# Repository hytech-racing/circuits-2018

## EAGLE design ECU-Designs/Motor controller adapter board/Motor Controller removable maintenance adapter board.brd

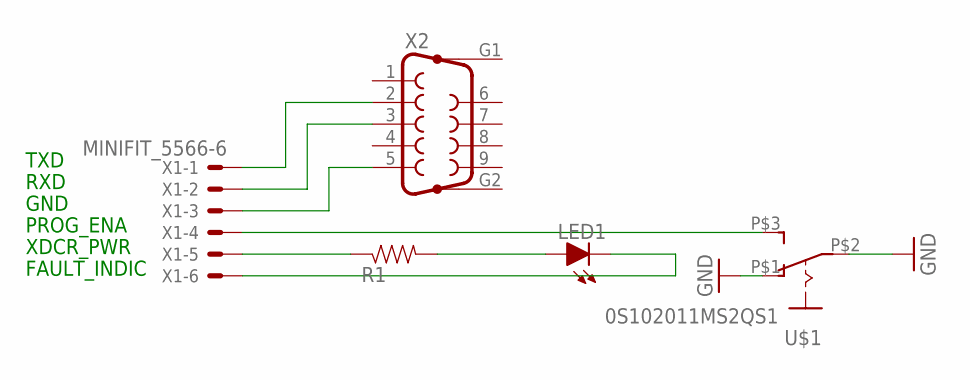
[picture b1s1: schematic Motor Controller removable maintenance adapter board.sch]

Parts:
LED1: LED-0805; LED-805
R1: RESISTOR0805-RES; 0805
U$1: 0S102011MS2QS1
X1: MINIFIT_5566-6
X2: F09HP

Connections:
GND: U$1.P$1 (O), U$1.P$2
unnamed: LED1.A, R1.2
unnamed: R1.1, X1.5
unnamed: LED1.C, X1.6
unnamed: U$1.P$3 (S), X1.4
unnamed: X1.1, X2.2
unnamed: X1.2, X2.3
unnamed: X1.3, X2.5

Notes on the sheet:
TXD
RXD
GND
PROG_ENA
XDCR_PWR
FAULT_INDIC

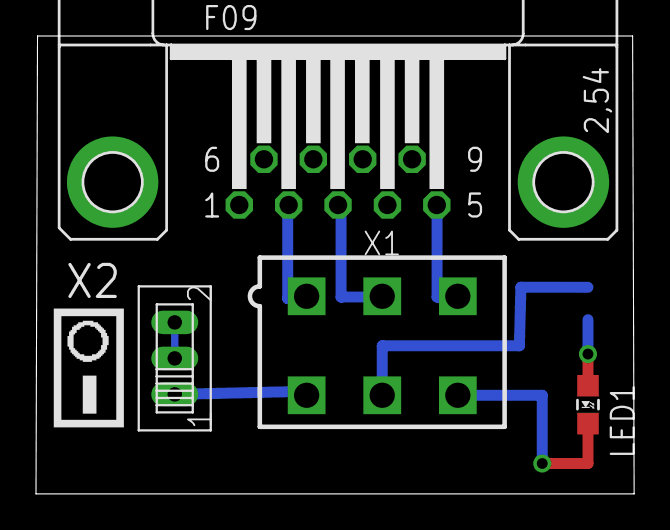
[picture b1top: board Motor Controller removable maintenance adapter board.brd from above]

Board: 2 copper layers, 33.2 x 25.4 mm, 5 parts (1 on the bottom side), 8 nets.

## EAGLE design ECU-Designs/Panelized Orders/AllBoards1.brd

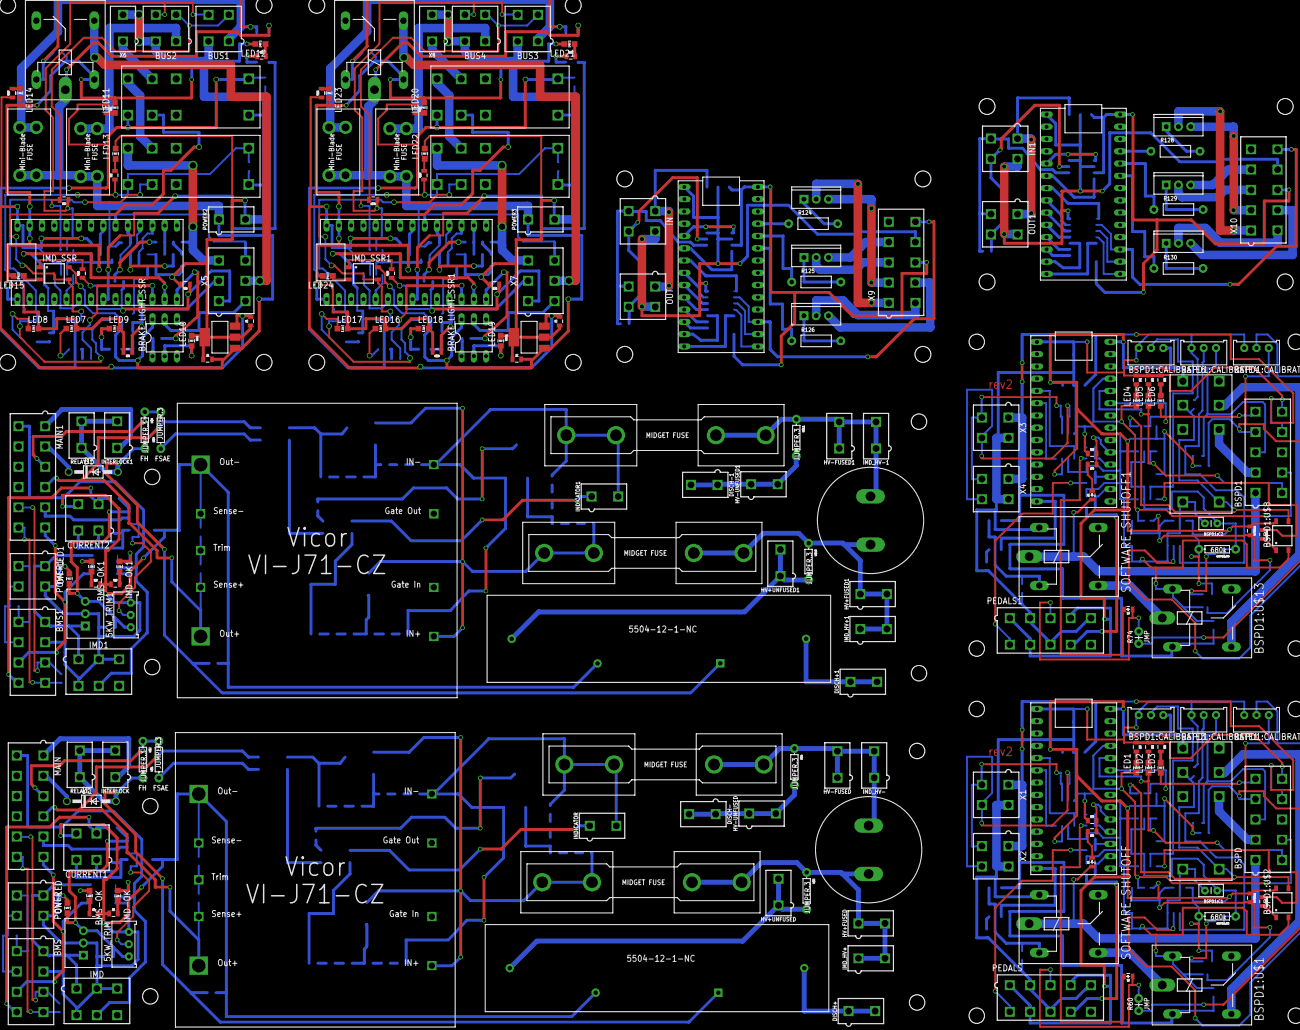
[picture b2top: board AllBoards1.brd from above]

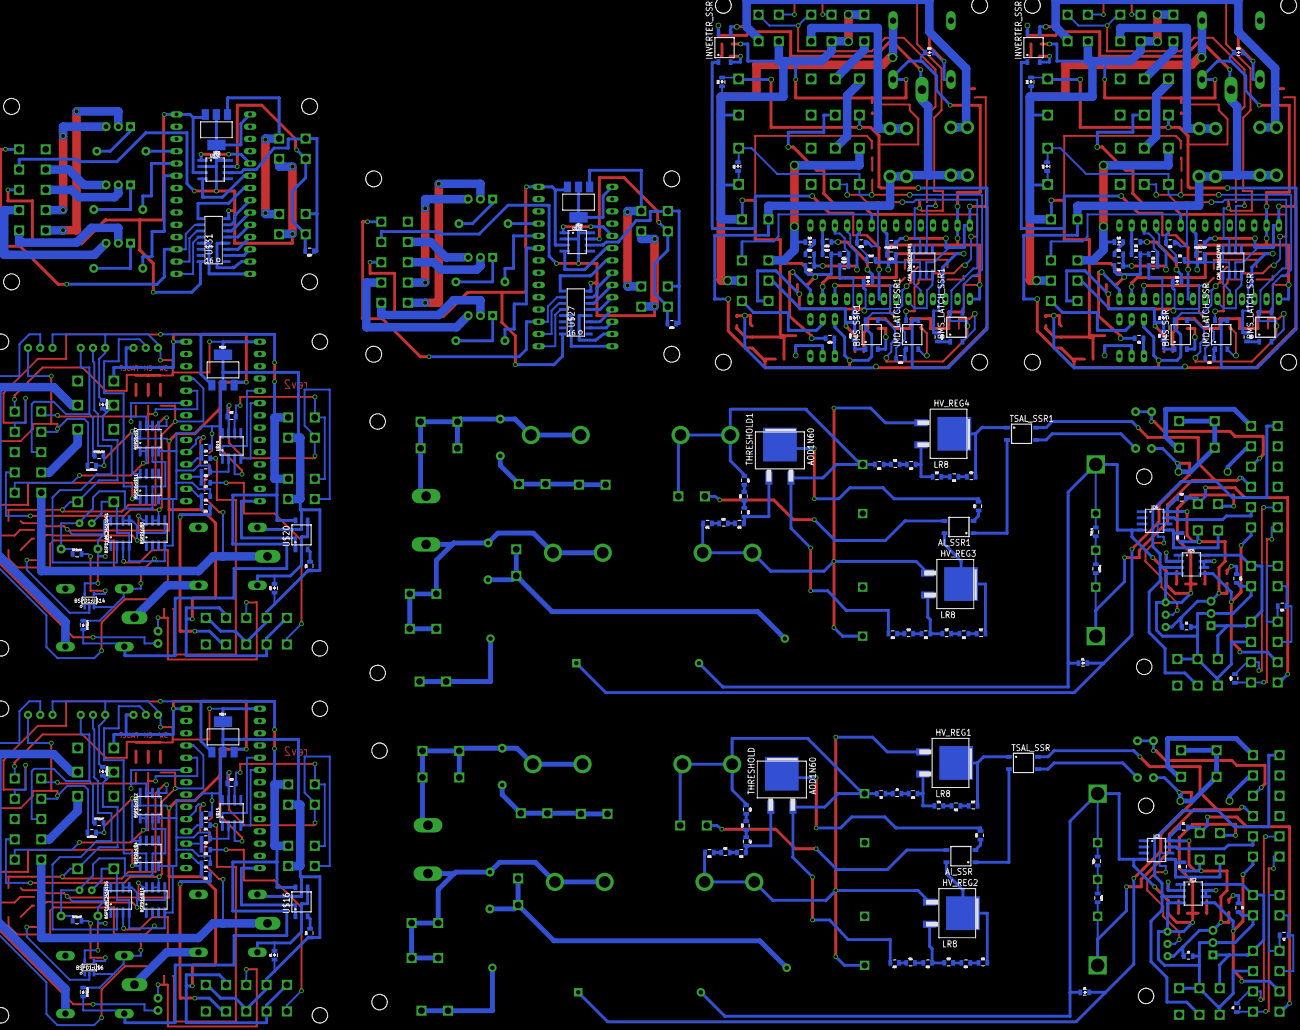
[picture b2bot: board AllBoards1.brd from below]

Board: 2 copper layers, 378 parts (172 on the bottom side), 344 nets.

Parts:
5KW_TRIM, 5KW_TRIM1: TRIMPOT_3296
AI_SSR, AI_SSR1: CPC1002N; SOP04
BMS, BMS1: MINIFIT_5566-8
BMS-OK, BMS-OK1: LED-805
BMS_LATCH_SSR, BMS_LATCH_SSR1: CPC1002N; SOP04
BMS_SSR, BMS_SSR1: CPC1002N; SOP04
BOARD_TEMP, BOARD_TEMP1: THERMISTOR_NCP21; 0805
BRAKE_LIGHT_SSR, BRAKE_LIGHT_SSR1: SOLID_STATE_RELAY_VO14642AT; DIL06
BSPD, BSPD1: MINIFIT_5566-10
BSPD1:C1, BSPD1:C2: .47u; CAP-PTH-SMALLEZ
BSPD1:CALIBRATE1, BSPD1:CALIBRATE2, BSPD1:CALIBRATE3, BSPD1:CALIBRATE4, BSPD1:CALIBRATE5, BSPD1:CALIBRATE6: TRIMPOT_3296
BSPD1:D1, BSPD1:D2, BSPD1:D3, BSPD1:D4: DIODE0805; 0805_D
BSPD1:MC34161DG, BSPD1:MC34161DG1: SOIC-08
BSPD1:R1, BSPD1:R2, BSPD1:R4, BSPD1:R7, BSPD1:R11, BSPD1:R12: 10k; 0805
BSPD1:R3, BSPD1:R8: 330; 0805
BSPD1:R5, BSPD1:R9: 680k; AXIAL-0.3EZ
BSPD1:R6, BSPD1:R10: 680; 0805
BSPD1:U$1, BSPD1:U$13: G5LE; ZF112
BSPD1:U$2, BSPD1:U$8: CPC1002N; SOP04
BSPD1:U$3, BSPD1:U$9: JW2SN-DC5V; JW2SN
BSPD1:U$4, BSPD1:U$5, BSPD1:U$7, BSPD1:U$10, BSPD1:U$11, BSPD1:U$12: MCP6002SOIC; SOIC-08
BSPD1:U$6, BSPD1:U$14: SN74LVC1G07; SOT-23-5
BUS1, BUS2, BUS3, BUS4: MINIFIT_5566-4
C1, C4: 220uF; LLS2V221MELZ
C2, C3: 1uF; 0805
C5, C7: .22uF; 0805
C6, C8: .1uF; 0805
CAN_TRANSCEIVER, CAN_TRANSCEIVER1: MCP2551; SOIC-08
CURRENT1, CURRENT2: MINIFIT_5566-4
D1, D3: DIODE; DO-41
D2, D4, D5, D6, D7, D8, D9, D10, D11, D12, D13, D14, D15, D16, D17, D18, D19, D20, D21, D22: DIODE0805; 0805_D
DISCH+, DISCH+1: TO DISCHARGE +; MINIFIT_5566-2
DISCH-, DISCH-1: TO DISCHARGE -; MINIFIT_5566-2
FUSE, FUSE1, FUSE2, FUSE3: 250mA; 1A3400_38.1MM
FUSE_BUS_1, FUSE_BUS_2, FUSE_BUS_3, FUSE_BUS_4: 5A; MINI-BLADE_FUSE_HOLDER
HV+FUSED, HV+FUSED1: MINIFIT_5566-2
HV+UNFUSED, HV+UNFUSED1: CONNECTOR FSAE; MINIFIT_5566-2
HV-FUSED, HV-FUSED1: MINIFIT_5566-2
HV-UNFUSED, HV-UNFUSED1: CONNECTOR FSAE; MINIFIT_5566-2
HV_REG1, HV_REG2, HV_REG3, HV_REG4: LR8; TO-252
IC1, IC4: TO-220
IC2, IC3, IC5, IC6: MCP6002SOIC; SOIC-08
IMD, IMD1: MINIFIT_5566-6
IMD-OK, IMD-OK1: LED-805
IMD_HV+, IMD_HV+1: MINIFIT_5566-2
IMD_HV-, IMD_HV-1: MINIFIT_5566-2
IMD_LATCH_SSR, IMD_LATCH_SSR1: CPC1002N; SOP04
IMD_SHUTDOWN, IMD_SHUTDOWN1, IMD_SHUTDOWN2, IMD_SHUTDOWN3: G2RL-2-DC12; G2RL-2
IMD_SSR, IMD_SSR1: CPC1002N; SOP04
IN, IN1: MINIFIT_5566-4
INDICATOR, INDICATOR1: MINIFIT_5566-2
INTERLOCK, INTERLOCK1: MINIFIT_5566-2
INVERTER_SSR, INVERTER_SSR1: CPC1002N; SOP04
LED1, LED2, LED3, LED4, LED5, LED6, LED7, LED8, LED9, LED10, LED11, LED12, LED13, LED14, LED15, LED16, LED17, LED18, LED19, LED20, LED21, LED22, LED23, LED24: LED-805
MAIN, MAIN1: MINIFIT_5566-12
ON-LED, ON-LED1: LED-805
OUT, OUT1: MINIFIT_5566-4
PEDALS, PEDALS1: MINIFIT_5566-10
POWER, POWER1: MINIFIT_5566-4
POWER2, POWER3: MINIFIT_5566-2
R1, R2, R33, R35, R53, R67, R87, R108, R123, R127: 120; 0805
R3, R4, R29, R30: 0805
R5, R34, R61, R75, R82, R83, R84, R85, R96, R103, R104, R105, R106, R117: 100; 0805
R6, R7, R28, R32, R62, R63, R64, R76, R77, R78, R95, R98, R116, R119: 10k; 0805
R8, R9, R10, R50, R51, R52: 8.2k; 0805
R11, R12, R13, R23, R24, R25, R27, R39, R44, R45, R46, R47: 2k; 0805
R14, R15, R16, R36, R40, R41: 500k; 0805
R17, R18, R19, R37, R42, R43: 40k; 0805
R20, R21, R22, R31, R48, R49: 20k; 0805
R26, R38: 1k; 0805
R54, R55, R56, R68, R69, R70: 15k; 0805
R57, R58, R59, R71, R72, R73: 150; 0805
R60, R74: JMP; AXIAL-0.1
R65, R79, R81, R89, R91, R93, R102, R110, R112, R114: 43k; 0805
R66, R80, R88, R90, R92, R94, R109, R111, R113, R115: 12k; 0805
R86, R97, R107, R118: 820; 0805
R99, R120: 2.2k; 0805
R100, R121: 270; 0805
R101, R122: 680; 0805
R124, R125, R126, R128, R129, R130: AXIAL-0.4
REG, REG1: 5V; SOT223
RELAYS, RELAYS1: MINIFIT_5566-2
SOFTWARE_SHUTOFF, SOFTWARE_SHUTOFF1: G5LE; ZF112
T1, T2, T3, T4, T5, T6: N-CHANNEL_MOSFETGENERIC; TO-220-SINK
THRESHOLD, THRESHOLD1: AOD1N60; TO-252
TRIM+, TRIM+1: 0805
TRIM-, TRIM-1: 0805
TSAL_SSR, TSAL_SSR1: CPC1002N; SOP04
U$1, U$2, U$3, U$4, U$8, U$9, U$10, U$11: JUMPER.3; AXIAL-0.3
U$5, U$7: HV_DCDC_VI-J71-CZ
U$6, U$12: 5504-12-1-NC
U$13, U$17, U$22, U$24, U$25, U$29: TEENSY_3.2_SIMPLE
U$14, U$18, U$28, U$32: SOT223
U$15, U$19, U$26, U$30: MCP2551; SOIC-08
U$16, U$20: CPC1002N; SOP04
U$21, U$23: G5LE; ZF112
U$27, U$31: CD4040BSOIC; SOIC-16
X1, X2, X3, X4: MINIFIT_5566-4
X5, X7: MINIFIT_5566-6
X6, X8: MINIFIT_5566-2
X9, X10: CONNECTOR-10; MINIFIT_5566-10

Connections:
5KW_TRIG: 5KW_TRIM.2, IC3.6
5KW_TRIG1: 5KW_TRIM1.2, IC6.6
12VSUPPLY_READ: R93.2, R94.1, U$22.A3
12VSUPPLY_READ1: R114.2, R115.1, U$24.A3
12V_F1: BUS1.1, FUSE_BUS_1.L1, FUSE_BUS_1.L2
12V_F2: BUS2.1, FUSE_BUS_2.R1, FUSE_BUS_2.R2
12V_F3: BUS3.1, FUSE_BUS_3.L1, FUSE_BUS_3.L2
12V_F4: BUS4.1, FUSE_BUS_4.R1, FUSE_BUS_4.R2
+5V: 5KW_TRIM.1, C3.1, CURRENT1.1, IC1.3, IC3.8, ON-LED.A, R6.1, R7.1
+5V1: 5KW_TRIM1.1, C2.1, CURRENT2.1, IC4.3, IC6.8, ON-LED1.A, R28.1, R32.1
+5V2: BSPD1:CALIBRATE3.1, BSPD1:MC34161DG.8, BSPD1:R1.1, BSPD1:R4.1, BSPD1:R5.P$2, BSPD1:R7.2, BSPD1:U$2.4, BSPD1:U$3.4, BSPD1:U$4.8, BSPD1:U$6.5, BSPD1:U$10.8, BSPD1:U$12.8, PEDALS.1, PEDALS.4, PEDALS.7, U$13.VIN, U$14.3, U$15.3
+5V3: BSPD1:CALIBRATE6.1, BSPD1:MC34161DG1.8, BSPD1:R2.1, BSPD1:R9.P$2, BSPD1:R11.1, BSPD1:R12.2, BSPD1:U$5.8, BSPD1:U$7.8, BSPD1:U$8.4, BSPD1:U$9.4, BSPD1:U$11.8, BSPD1:U$14.5, PEDALS1.1, PEDALS1.4, PEDALS1.7, U$17.VIN, U$18.3, U$19.3
+5V4: BOARD_TEMP.1, C6.2, CAN_TRANSCEIVER.3, R100.1, REG.3, U$22.VIN
+5V5: BOARD_TEMP1.1, C8.2, CAN_TRANSCEIVER1.3, R121.1, REG1.3, U$24.VIN
+5V6: U$25.VIN, U$26.3, U$27.16, U$28.3, X9.8
+5V7: U$29.VIN, U$30.3, U$31.16, U$32.3, X10.8
+12V: BMS.1, IC1.1, IC2.8, IMD.1, POWER.1
+12V1: BMS1.1, IC4.1, IC5.8, IMD1.1, POWER1.1
+12V2: BSPD.9, BSPD1:D2.C, BSPD1:U$1.2, U$14.1, U$16.4, X1.1, X2.1
+12V3: BSPD1.9, BSPD1:D4.C, BSPD1:U$13.2, U$18.1, U$20.4, X3.1, X4.1
+12V4: BMS_SSR.4, BRAKE_LIGHT_SSR.6, C5.2, FUSE_BUS_1.R1, FUSE_BUS_1.R2, FUSE_BUS_2.L1, FUSE_BUS_2.L2, IMD_SSR.4, INVERTER_SSR.4, POWER2.1, R93.1, REG.1, U$21.P
+12V5: BMS_SSR1.4, BRAKE_LIGHT_SSR1.6, C7.2, FUSE_BUS_3.R1, FUSE_BUS_3.R2, FUSE_BUS_4.L1, FUSE_BUS_4.L2, IMD_SSR1.4, INVERTER_SSR1.4, POWER3.1, R114.1, REG1.1, U$23.P
+12V6: IN.1, OUT.1, U$28.1
+12V7: IN1.1, OUT1.1, U$32.1
BMS_COIL_PWR: BMS_LATCH_SSR.3, D15.C, IMD_SHUTDOWN1.4, IMD_SHUTDOWN1.COIL-, R97.1
BMS_COIL_PWR1: BMS_LATCH_SSR1.3, D21.C, IMD_SHUTDOWN3.4, IMD_SHUTDOWN3.COIL-, R118.1
BMS_OK: BMS.7, IC2.5, MAIN.6
BMS_OK1: BMS1.7, IC5.5, MAIN1.6
BMS_OK2: D12.A, R83.2, R98.1, X5.2
BMS_OK3: D18.A, R104.2, R119.1, X7.2
BMS_OK_READ: R89.2, R90.1, U$22.A1
BMS_OK_READ1: R110.2, R111.1, U$24.A1
BMS_PWR_STEP: BMS_LATCH_SSR.4, BMS_SSR.3, IMD_SHUTDOWN1.3
BMS_PWR_STEP1: BMS_LATCH_SSR1.4, BMS_SSR1.3, IMD_SHUTDOWN3.3
BSPD1:N$1: BSPD1:D1.C, BSPD1:U$2.3, BSPD1:U$3.3, BSPD1:U$3.COIL-, BSPD1:U$12.5
BSPD1:N$2: BSPD1:R3.2, BSPD1:U$6.4
BSPD1:N$3: BSPD1:R6.2, BSPD1:U$2.1
BSPD1:N$4: BSPD1:CALIBRATE5.2, BSPD1:MC34161DG1.3
BSPD1:N$5: BSPD1:CALIBRATE2.2, BSPD1:MC34161DG.3
BSPD1:N$6: BSPD1:CALIBRATE1.2, BSPD1:MC34161DG.2
BSPD1:N$7: BSPD1:CALIBRATE3.2, BSPD1:U$4.2
BSPD1:N$8: BSPD1:CALIBRATE4.2, BSPD1:MC34161DG1.2
BSPD1:N$9: BSPD1:R6.1, BSPD1:U$4.1
BSPD1:N$10: BSPD1:MC34161DG.5, BSPD1:MC34161DG.6, BSPD1:R1.2, BSPD1:U$6.2, BSPD1:U$10.5
BSPD1:N$11: BSPD1:R10.1, BSPD1:U$11.1
BSPD1:N$12: BSPD1:C2.1, BSPD1:R8.1, BSPD1:R9.P$1, BSPD1:U$7.3, BSPD1:U$11.3
BSPD1:N$13: BSPD1:C1.1, BSPD1:R3.1, BSPD1:R5.P$1, BSPD1:U$4.3, BSPD1:U$12.3
BSPD1:N$14: BSPD1:CALIBRATE6.2, BSPD1:U$11.2
BSPD1:N$15: BSPD1:D3.C, BSPD1:U$7.5, BSPD1:U$8.3, BSPD1:U$9.3, BSPD1:U$9.COIL-
BSPD1:N$16: BSPD1:MC34161DG1.5, BSPD1:MC34161DG1.6, BSPD1:R2.2, BSPD1:U$5.5, BSPD1:U$14.2
BSPD1:N$17: BSPD1:R8.2, BSPD1:U$14.4
BSPD1:N$18: BSPD1:R10.2, BSPD1:U$8.1
BSPD1:SHUTDOWN_C: BSPD1:U$1.S, BSPD1:U$3.6
BSPD1:SHUTDOWN_C1: BSPD1:U$9.6, BSPD1:U$13.S
BSPD_CUR_FAULT: IC3.7, MAIN.5
BSPD_CUR_FAULT1: IC6.7, MAIN1.5
CANH: BUS1.4, BUS2.4, CAN_TRANSCEIVER.7, R87.1
CANH1: BUS3.4, BUS4.4, CAN_TRANSCEIVER1.7, R108.1
CANH2: IN.4, OUT.4, R123.2, U$26.7
CANH3: IN1.4, OUT1.4, R127.2, U$30.7
CANH_IN: BMS.6, POWER.4, R2.1
CANH_IN1: BMS1.6, POWER1.4, R35.1
CANH_OUT: BMS.4, MAIN.12, R1.1
CANH_OUT1: BMS1.4, MAIN1.12, R33.1
CANL: BUS1.3, BUS2.3, CAN_TRANSCEIVER.6, R87.2
CANL1: BUS3.3, BUS4.3, CAN_TRANSCEIVER1.6, R108.2
CANL2: IN.3, OUT.3, R123.1, U$26.6
CANL3: IN1.3, OUT1.3, R127.1, U$30.6
CANL_IN: BMS.5, POWER.3, R2.2
CANL_IN1: BMS1.5, POWER1.3, R35.2
CANL_OUT: BMS.3, MAIN.11, R1.2
CANL_OUT1: BMS1.3, MAIN1.11, R33.2
CUR_SENSE: CURRENT1.2, IC3.5, R6.2
CUR_SENSE1: CURRENT2.2, IC6.5, R32.2
DISCHARGE1: HV+UNFUSED.1, HV+UNFUSED.2, U$3.P$2, U$12.CONTACT1
DISCHARGE2: DISCH+.1, DISCH+.2, U$12.CONTACT2
DISCHARGE3: DISCH-.1, DISCH-.2, HV-UNFUSED.1, HV-UNFUSED.2, U$4.P$2
DISCHARGE4: DISCH+1.1, DISCH+1.2, U$6.CONTACT2
DISCHARGE5: HV+UNFUSED1.1, HV+UNFUSED1.2, U$6.CONTACT1, U$10.P$2
DISCHARGE6: DISCH-1.1, DISCH-1.2, HV-UNFUSED1.1, HV-UNFUSED1.2, U$11.P$2
FAN1-: T1.2, X9.1
FAN1-1: T4.2, X10.1
FAN2-: T2.2, X9.3
FAN2-1: T5.2, X10.3
FAN3-: T3.2, X9.6
FAN3-1: T6.2, X10.6
GND: 5KW_TRIM.3, BMS.2, C3.2, CURRENT1.4, D2.A, IC1.2, IC2.4, IC3.4, IMD.2, IMD.3, IMD.4, POWER.2, R3.1, R4.2, R5.2, TRIM-.2, U$5.8SENSE-, U$5.9VOUT-, U$12.COIL-
GND1: 5KW_TRIM1.3, BMS1.2, C2.2, CURRENT2.4, D4.A, IC4.2, IC5.4, IC6.4, IMD1.2, IMD1.3, IMD1.4, POWER1.2, R29.1, R30.2, R34.2, TRIM-1.2, U$6.COIL-, U$7.8SENSE-, U$7.9VOUT-
GND2: BSPD.10, BSPD1:C1.2, BSPD1:CALIBRATE1.3, BSPD1:CALIBRATE2.3, BSPD1:CALIBRATE3.3, BSPD1:D1.A, BSPD1:D2.A, BSPD1:MC34161DG.4, BSPD1:MC34161DG.7, BSPD1:U$1.1, BSPD1:U$2.2, BSPD1:U$3.COIL+, BSPD1:U$4.4, BSPD1:U$6.3, BSPD1:U$10.4, BSPD1:U$12.4, D7.A, PEDALS.2, PEDALS.5, PEDALS.8, R54.1, R55.1, R56.1, R57.1, R58.1, R59.1, R61.1, R66.1, SOFTWARE_SHUTOFF.1, U$13.GND, U$14.2, U$14.4, U$15.2, U$15.8, X1.2, X2.2
GND3: BSPD1.10, BSPD1:C2.2, BSPD1:CALIBRATE4.3, BSPD1:CALIBRATE5.3, BSPD1:CALIBRATE6.3, BSPD1:D3.A, BSPD1:D4.A, BSPD1:MC34161DG1.4, BSPD1:MC34161DG1.7, BSPD1:U$5.4, BSPD1:U$7.4, BSPD1:U$8.2, BSPD1:U$9.COIL+, BSPD1:U$11.4, BSPD1:U$13.1, BSPD1:U$14.3, D10.A, PEDALS1.2, PEDALS1.5, PEDALS1.8, R68.1, R69.1, R70.1, R71.1, R72.1, R73.1, R75.1, R80.1, SOFTWARE_SHUTOFF1.1, U$17.GND, U$18.2, U$18.4, U$19.2, U$19.8, X3.2, X4.2
GND4: BUS1.2, BUS2.2, C5.1, C6.1, CAN_TRANSCEIVER.2, CAN_TRANSCEIVER.8, D14.A, D15.A, D16.A, IMD_SHUTDOWN.COIL+, IMD_SHUTDOWN1.COIL+, LED7.C, LED8.C, LED9.C, LED10.C, LED11.C, LED12.C, LED13.C, LED14.C, LED15.C, POWER2.2, R88.2, R90.2, R92.2, R94.2, R95.1, R98.2, R99.2, REG.2, REG.4, U$21.2, U$22.AGND, U$22.GND, X6.2
GND5: BUS3.2, BUS4.2, C7.1, C8.1, CAN_TRANSCEIVER1.2, CAN_TRANSCEIVER1.8, D20.A, D21.A, D22.A, IMD_SHUTDOWN2.COIL+, IMD_SHUTDOWN3.COIL+, LED16.C, LED17.C, LED18.C, LED19.C, LED20.C, LED21.C, LED22.C, LED23.C, LED24.C, POWER3.2, R109.2, R111.2, R113.2, R115.2, R116.1, R119.2, R120.2, REG1.2, REG1.4, U$23.2, U$24.AGND, U$24.GND, X8.2
GND6: IN.2, OUT.2, U$25.GND, U$26.2, U$26.8, U$27.8, U$28.2, U$28.4, X9.9
GND7: T1.3, X9.2
GND8: T2.3, X9.4
GND9: T3.3, X9.7
GND10: IN1.2, OUT1.2, U$29.GND, U$30.2, U$30.8, U$31.8, U$32.2, U$32.4, X10.9
GND11: T4.3, X10.2
GND12: T5.3, X10.4
GND13: T6.3, X10.7
HV+FUSED: C1.P$1, FUSE.P1, FUSE.P2, HV+FUSED.1, HV+FUSED.2, IMD_HV+.1, IMD_HV+.2, U$3.P$1
HV+FUSED1: FUSE2.N3, FUSE2.N4, HV_REG3.1, HV_REG4.1, R41.2, U$7.1VIN+
HV+FUSED2: C4.P$1, FUSE2.P1, FUSE2.P2, HV+FUSED1.1, HV+FUSED1.2, IMD_HV+1.1, IMD_HV+1.2, U$10.P$1
HV+FUSED250: FUSE.N3, FUSE.N4, HV_REG1.1, HV_REG2.1, R14.2, U$5.1VIN+
HV-FUSED: C1.P$2, FUSE1.P1, FUSE1.P2, HV-FUSED.1, HV-FUSED.2, IMD_HV-.1, IMD_HV-.2, U$4.P$1
HV-FUSED1: C4.P$2, FUSE3.P1, FUSE3.P2, HV-FUSED1.1, HV-FUSED1.2, IMD_HV-1.1, IMD_HV-1.2, U$11.P$1
HV-FUSED2: FUSE3.N3, FUSE3.N4, INDICATOR1.2, R37.1, R49.2, R52.2, THRESHOLD1.3, U$7.4VIN-
HV-FUSED250: FUSE1.N3, FUSE1.N4, INDICATOR.2, R8.2, R19.1, R20.2, THRESHOLD.3, U$5.4VIN-
INVERTER_SUPPLY: U$21.S, X5.5
INVERTER_SUPPLY1: U$23.S, X7.5
unnamed: AI_SSR.4, HV_REG2.2(TAB), R25.2
unnamed: HV_REG1.2(TAB), R13.2, TSAL_SSR.1
unnamed: ON-LED.C, R5.1
unnamed: TSAL_SSR.3, U$1.P$1
unnamed: AI_SSR.2, R26.1
unnamed: AI_SSR.1, TSAL_SSR.2
unnamed: AI_SSR.3, INDICATOR.1
unnamed: R8.1, R9.1
unnamed: R26.2, THRESHOLD.2(TAB)
unnamed: R14.1, R15.1
unnamed: R15.2, R16.2
unnamed: R17.1, R18.1
unnamed: R18.2, R19.2
unnamed: R9.2, R10.2
unnamed: HV_REG2.3, R22.1, R23.1
unnamed: R11.2, R12.2
unnamed: R12.1, R13.1
unnamed: HV_REG1.3, R10.1, R11.1
unnamed: R23.2, R24.2
unnamed: R24.1, R25.1
unnamed: R21.2, R22.2
unnamed: R16.1, R17.2, THRESHOLD.1
unnamed: R20.1, R21.1
unnamed: AI_SSR1.4, HV_REG3.2(TAB), R47.2
unnamed: HV_REG3.3, R27.1, R31.1
unnamed: IC5.1, IC5.2, IMD-OK1.A
unnamed: BMS-OK1.A, IC5.6, IC5.7
unnamed: BMS-OK1.C, R30.1
unnamed: IMD-OK1.C, R29.2
unnamed: ON-LED1.C, R34.1
unnamed: HV_REG4.2(TAB), R39.2, TSAL_SSR1.1
unnamed: R40.1, R41.1
unnamed: R36.2, R40.2
unnamed: R42.1, R43.1
unnamed: R37.2, R42.2
unnamed: TSAL_SSR1.3, U$8.P$1
unnamed: AI_SSR1.2, R38.1
unnamed: AI_SSR1.1, TSAL_SSR1.2
unnamed: AI_SSR1.3, INDICATOR1.1
unnamed: HV_REG4.3, R45.1, R50.1
unnamed: IC2.1, IC2.2, IMD-OK.A
unnamed: BMS-OK.A, IC2.6, IC2.7
unnamed: BMS-OK.C, R4.1
unnamed: IMD-OK.C, R3.2
unnamed: R50.2, R51.2
unnamed: R51.1, R52.1
unnamed: R36.1, R43.2, THRESHOLD1.1
unnamed: R44.2, R45.2
unnamed: R39.1, R44.1
unnamed: R38.2, THRESHOLD1.2(TAB)
unnamed: R27.2, R46.2
unnamed: R46.1, R47.1
unnamed: R31.2, R48.2
unnamed: R48.1, R49.1
unnamed: R53.2, U$15.6, X1.3, X2.3
unnamed: R53.1, U$15.7, X1.4, X2.4
unnamed: U$13.D4(CANRX), U$15.4
unnamed: U$13.D3(CANTX), U$15.1
unnamed: PEDALS.6, R63.1
unnamed: R54.2, R62.2, U$13.A0
unnamed: LED1.C, R57.2
unnamed: LED2.C, R58.2
unnamed: LED3.C, R59.2
unnamed: R61.2, U$16.2
unnamed: R55.2, R63.2, U$13.A1
unnamed: PEDALS.9, R62.1
unnamed: R56.2, R64.2, U$13.A2
unnamed: D5.A, PEDALS.3, R60.P$2
unnamed: D5.C, R64.1
unnamed: D7.C, SOFTWARE_SHUTOFF.2, U$16.3
unnamed: D6.C, R65.2
unnamed: R67.2, U$19.6, X3.3, X4.3
unnamed: R67.1, U$19.7, X3.4, X4.4
unnamed: U$17.D4(CANRX), U$19.4
unnamed: U$17.D3(CANTX), U$19.1
unnamed: PEDALS1.6, R77.1
unnamed: R68.2, R76.2, U$17.A0
unnamed: LED4.C, R71.2
unnamed: LED5.C, R72.2
unnamed: LED6.C, R73.2
unnamed: R75.2, U$20.2
unnamed: R69.2, R77.2, U$17.A1
unnamed: PEDALS1.9, R76.1
unnamed: R70.2, R78.2, U$17.A2
unnamed: D8.A, PEDALS1.3, R74.P$2
unnamed: D8.C, R78.1
unnamed: D10.C, SOFTWARE_SHUTOFF1.2, U$20.3
unnamed: D9.C, R79.2
unnamed: CAN_TRANSCEIVER.4, U$22.D4(CANRX)
unnamed: CAN_TRANSCEIVER.1, U$22.D3(CANTX)
unnamed: D16.C, IMD_LATCH_SSR.3, IMD_SHUTDOWN.4, IMD_SHUTDOWN.COIL-, R86.1
unnamed: R82.2, U$22.D12
unnamed: BRAKE_LIGHT_SSR.5, X5.4
unnamed: BOARD_TEMP.2, R95.2, U$22.A5
unnamed: R85.1, U$22.D11
unnamed: IMD_LATCH_SSR.2, LED7.A
unnamed: BMS_SSR.2, LED9.A
unnamed: BMS_SSR.1, R83.1
unnamed: BRAKE_LIGHT_SSR.2, LED10.A
unnamed: BRAKE_LIGHT_SSR.1, R82.1
unnamed: LED11.A, R86.2
unnamed: INVERTER_SSR.1, U$22.D6
unnamed: U$22.A4, X5.6
unnamed: D11.C, R81.1
unnamed: D12.C, R89.1
unnamed: D13.C, R91.1
unnamed: D14.C, INVERTER_SSR.3, U$21.1
unnamed: INVERTER_SSR.2, R96.1
unnamed: LED12.A, R96.2
unnamed: IMD_LATCH_SSR.1, R84.1
unnamed: R84.2, U$22.D10(TX2)
unnamed: BMS_LATCH_SSR.2, LED8.A
unnamed: BMS_LATCH_SSR.1, R85.2
unnamed: LED13.A, R97.2
unnamed: LED14.A, R100.2
unnamed: IMD_LATCH_SSR.4, IMD_SHUTDOWN.3, IMD_SSR.3
unnamed: IMD_SSR.2, LED15.A
unnamed: IMD_SSR.1, R101.2
unnamed: CAN_TRANSCEIVER1.4, U$24.D4(CANRX)
unnamed: CAN_TRANSCEIVER1.1, U$24.D3(CANTX)
unnamed: D22.C, IMD_LATCH_SSR1.3, IMD_SHUTDOWN2.4, IMD_SHUTDOWN2.COIL-, R107.1
unnamed: R103.2, U$24.D12
unnamed: BRAKE_LIGHT_SSR1.5, X7.4
unnamed: BOARD_TEMP1.2, R116.2, U$24.A5
unnamed: R106.1, U$24.D11
unnamed: IMD_LATCH_SSR1.2, LED16.A
unnamed: BMS_SSR1.2, LED18.A
unnamed: BMS_SSR1.1, R104.1
unnamed: BRAKE_LIGHT_SSR1.2, LED19.A
unnamed: BRAKE_LIGHT_SSR1.1, R103.1
unnamed: LED20.A, R107.2
unnamed: INVERTER_SSR1.1, U$24.D6
unnamed: U$24.A4, X7.6
unnamed: D17.C, R102.1
unnamed: D18.C, R110.1
unnamed: D19.C, R112.1
unnamed: D20.C, INVERTER_SSR1.3, U$23.1
unnamed: INVERTER_SSR1.2, R117.1
unnamed: LED21.A, R117.2
unnamed: IMD_LATCH_SSR1.1, R105.1
unnamed: R105.2, U$24.D10(TX2)
unnamed: BMS_LATCH_SSR1.2, LED17.A
unnamed: BMS_LATCH_SSR1.1, R106.2
unnamed: LED22.A, R118.2
unnamed: LED23.A, R121.2
unnamed: IMD_LATCH_SSR1.4, IMD_SHUTDOWN2.3, IMD_SSR1.3
unnamed: IMD_SSR1.2, LED24.A
unnamed: IMD_SSR1.1, R122.2
unnamed: U$25.D3(CANTX), U$26.1
unnamed: U$25.D4(CANRX), U$26.4
unnamed: R124.P$2, T1.1
unnamed: R125.P$2, T2.1
unnamed: R126.P$2, T3.1
unnamed: R124.P$1, U$25.A9
unnamed: R125.P$1, U$25.A8
unnamed: R126.P$1, U$25.A7
unnamed: U$25.D5, U$27.9
unnamed: U$25.D6, U$27.7
unnamed: U$25.D7(RX3), U$27.6
unnamed: U$25.D8(TX3), U$27.5
unnamed: U$25.D9(RX2), U$27.3
unnamed: U$25.D10(TX2), U$27.2
unnamed: U$25.D11, U$27.4
unnamed: U$25.D12, U$27.13
unnamed: U$25.A0, U$27.11
unnamed: U$25.D13, U$27.12
unnamed: U$29.D3(CANTX), U$30.1
unnamed: U$29.D4(CANRX), U$30.4
unnamed: R128.P$2, T4.1
unnamed: R129.P$2, T5.1
unnamed: R130.P$2, T6.1
unnamed: R128.P$1, U$29.A9
unnamed: R129.P$1, U$29.A8
unnamed: R130.P$1, U$29.A7
unnamed: U$29.D5, U$31.9
unnamed: U$29.D6, U$31.7
unnamed: U$29.D7(RX3), U$31.6
unnamed: U$29.D8(TX3), U$31.5
unnamed: U$29.D9(RX2), U$31.3
unnamed: U$29.D10(TX2), U$31.2
unnamed: U$29.D11, U$31.4
unnamed: U$29.D12, U$31.13
unnamed: U$29.A0, U$31.11
unnamed: U$29.D13, U$31.12
OKHS: IC2.3, IMD.5, MAIN.7
OKHS1: IC5.3, IMD1.5, MAIN1.7
OKHS2: D11.A, R99.1, R101.1, X5.1
OKHS3: D17.A, R120.1, R122.1, X7.1
OKHS_READ: R81.2, R88.1, U$22.A0
OKHS_READ1: R102.2, R109.1, U$24.A0
PULSE: U$25.A1, U$27.10, X9.10
PULSE1: U$29.A1, U$31.10, X10.10
READ_CHARGE: BSPD.6, BSPD1:U$12.1, BSPD1:U$12.2, LED2.A, U$13.A8
READ_CHARGE1: BSPD1.6, BSPD1:U$7.1, BSPD1:U$7.2, LED5.A, U$17.A8
READ_FAULT: BSPD.5, BSPD1:U$12.6, BSPD1:U$12.7, LED3.A, U$13.A7
READ_FAULT1: BSPD1.5, BSPD1:U$7.6, BSPD1:U$7.7, LED6.A, U$17.A7
READ_SWITCH: BSPD.7, BSPD1:U$10.6, BSPD1:U$10.7, LED1.A, U$13.A9
READ_SWITCH1: BSPD1.7, BSPD1:U$5.6, BSPD1:U$5.7, LED4.A, U$17.A9
READ_UPSTREAM_SHUTDOWN: R65.1, R66.2, U$13.A3
READ_UPSTREAM_SHUTDOWN1: R79.1, R80.2, U$17.A3
SHUTDOWN1: D3.A, D4.C, INTERLOCK1.2, RELAYS1.1, RELAYS1.2, U$6.COIL+, U$9.P$2
SHUTDOWN2: INTERLOCK1.1, MAIN1.1
SHUTDOWN6: INTERLOCK.1, MAIN.1
SHUTDOWN7: D1.A, D2.C, INTERLOCK.2, RELAYS.1, RELAYS.2, U$2.P$2, U$12.COIL+
SHUTDOWN7_EXT_OUT: D1.C, MAIN.2
SHUTDOWN7_EXT_OUT1: D3.C, MAIN1.2
SHUTDOWN_A: BSPD.1, D6.A, SOFTWARE_SHUTOFF.P
SHUTDOWN_A1: BSPD1.1, D9.A, SOFTWARE_SHUTOFF1.P
SHUTDOWN_A2: IMD_SHUTDOWN.5, IMD_SHUTDOWN1.6
SHUTDOWN_A3: IMD_SHUTDOWN2.5, IMD_SHUTDOWN3.6
SHUTDOWN_B: BSPD1:U$1.P, SOFTWARE_SHUTOFF.S
SHUTDOWN_B1: BSPD1:U$13.P, SOFTWARE_SHUTOFF1.S
SHUTDOWN_B2: D13.A, IMD_SHUTDOWN1.5, X5.3
SHUTDOWN_B3: D19.A, IMD_SHUTDOWN3.5, X7.3
SHUTDOWN_D: BSPD.2, BSPD1:U$3.7
SHUTDOWN_D1: BSPD1.2, BSPD1:U$9.7
SHUTDOWN_OUT_READ: R91.2, R92.1, U$22.A2
SHUTDOWN_OUT_READ1: R112.2, R113.1, U$24.A2
SHUTDOWN_POWER: IMD_SHUTDOWN.6, X6.1
SHUTDOWN_POWER1: IMD_SHUTDOWN2.6, X8.1
SHUTDOWN_RELAY_CTRL: U$13.D12, U$16.1
SHUTDOWN_RELAY_CTRL1: U$17.D12, U$20.1
SIGNAL_BRAKE: BSPD.4, BSPD1:CALIBRATE2.1, BSPD1:R4.2, R60.P$1
SIGNAL_BRAKE1: BSPD1.4, BSPD1:CALIBRATE5.1, BSPD1:R11.2, R74.P$1
SIGNAL_CURRENT: BSPD.3, BSPD1:CALIBRATE1.1, BSPD1:R7.1
SIGNAL_CURRENT1: BSPD1.3, BSPD1:CALIBRATE4.1, BSPD1:R12.1
TEMP_SENSE: BMS.8, CURRENT1.3, R7.2
TEMP_SENSE1: BMS1.8, CURRENT2.3, R28.2
TRIM: TRIM+.1, TRIM-.1, U$5.7TRIM
TRIM1: TRIM+1.1, TRIM-1.1, U$7.7TRIM
TSAL+: MAIN.3, U$1.P$2, U$2.P$1
TSAL+1: MAIN1.3, U$8.P$2, U$9.P$1
TSVP+: MAIN.4, TRIM+.2, TSAL_SSR.4, U$5.5VOUT+, U$5.6SENSE+
TSVP+1: MAIN1.4, TRIM+1.2, TSAL_SSR1.4, U$7.5VOUT+, U$7.6SENSE+

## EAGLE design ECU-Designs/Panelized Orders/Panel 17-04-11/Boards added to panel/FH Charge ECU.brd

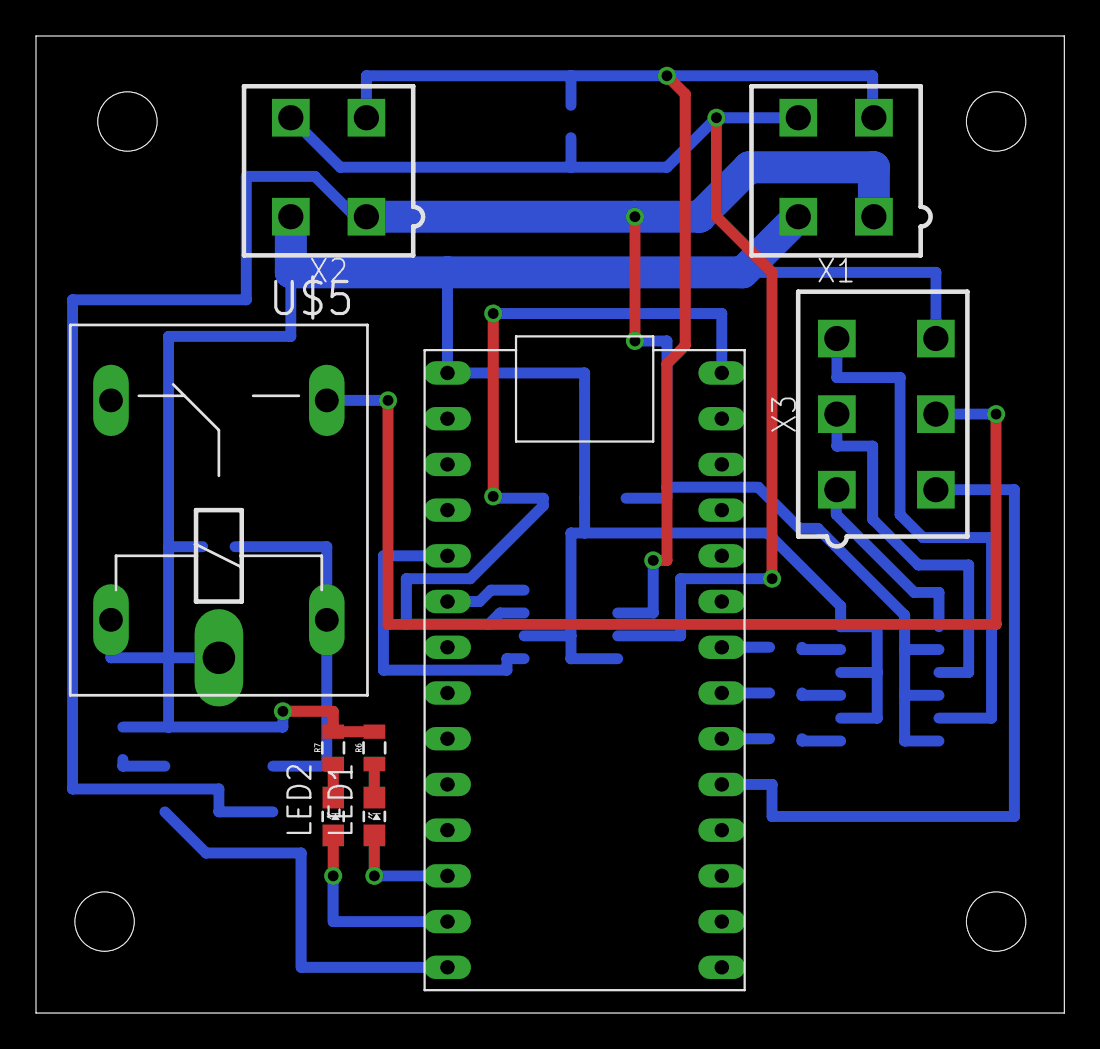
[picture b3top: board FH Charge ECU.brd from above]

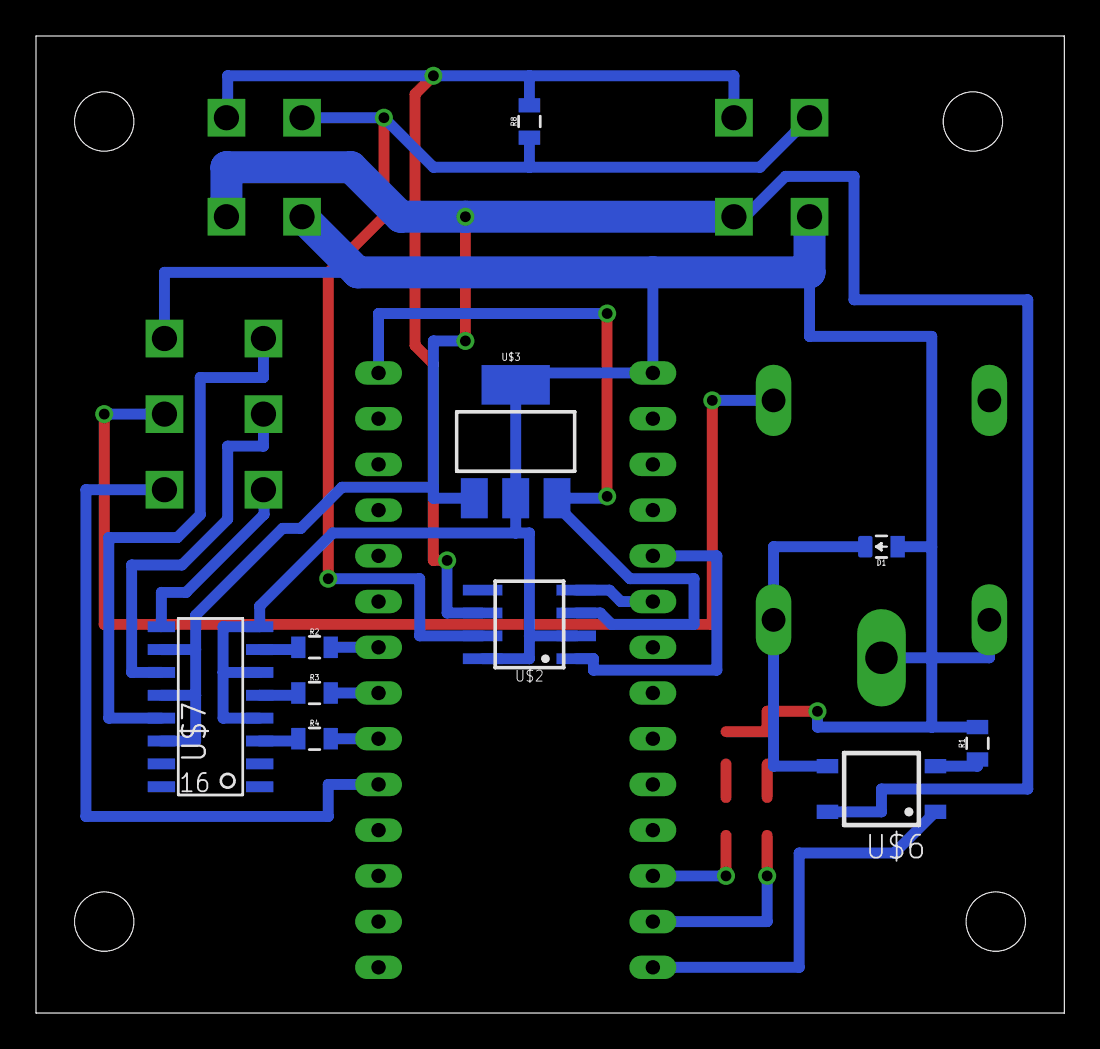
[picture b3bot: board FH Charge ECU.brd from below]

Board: 2 copper layers, 57.1 x 54.3 mm, 19 parts (10 on the bottom side), 25 nets.

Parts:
D1: DIODE0805; 0805_D
LED1, LED2: LED-805
R1, R2, R3, R4, R6, R7: 0805
R8: 120; 0805
U$1: TEENSY_3.2_SIMPLE
U$2: MCP2551; SOIC-08
U$3: SOT223
U$5: G5LE; ZF112
U$6: CPC1002N; SOP04
U$7: TLP291-4; SOIC-16
X1, X2: CONNECTOR-4; MINIFIT_5566-4
X3: CONNECTOR-6; MINIFIT_5566-6

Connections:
+12V: U$3.1, U$6.4, U$7.10, U$7.12, U$7.14, X1.1, X2.1
GND: D1.A, R1.2, R6.2, R7.2, U$1.GND, U$2.2, U$2.8, U$3.2, U$3.4, U$5.1, U$5.P, U$7.4, U$7.6, U$7.8, X1.2, X2.2, X3.6
unnamed: U$1.A3, X3.4
unnamed: U$1.VIN, U$2.3, U$3.3
unnamed: R8.2, U$2.6, X1.3, X2.3
unnamed: R8.1, U$2.7, X1.4, X2.4
unnamed: D1.C, U$5.2, U$6.3
unnamed: U$1.D3(CANTX), U$2.1
unnamed: U$1.D4(CANRX), U$2.4
unnamed: U$1.D12, U$6.1
unnamed: R1.1, U$6.2
unnamed: U$7.13, X3.3
unnamed: U$5.S, X3.5
unnamed: U$7.11, X3.2
unnamed: U$7.9, X3.1
unnamed: R4.2, U$1.A4
unnamed: R3.2, U$1.A5
unnamed: R2.2, U$1.A6
unnamed: R3.1, U$7.5
unnamed: R4.1, U$7.3
unnamed: R2.1, U$7.7
unnamed: LED1.C, R6.1
unnamed: LED2.C, R7.1
unnamed: LED1.A, U$1.D10(TX2)
unnamed: LED2.A, U$1.D11
